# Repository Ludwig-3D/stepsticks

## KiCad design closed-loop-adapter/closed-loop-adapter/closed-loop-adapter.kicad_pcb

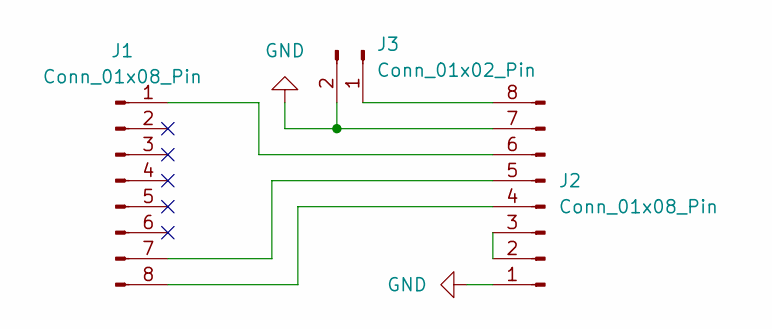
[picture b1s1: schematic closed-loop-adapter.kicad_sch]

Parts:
J1, J2: Conn_01x08_Pin; PinSocket_1x08_P2.54mm_Vertical
J3: Conn_01x02_Pin; JST_XH_S2B-XH-A-1_1x02_P2.50mm_Horizontal

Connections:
GND: J2.1, J2.7, J3.2
unnamed: J1.1, J2.6
unnamed: J1.7, J2.5
unnamed: J1.8, J2.4
unnamed: J2.2, J2.3
unnamed: J2.8, J3.1

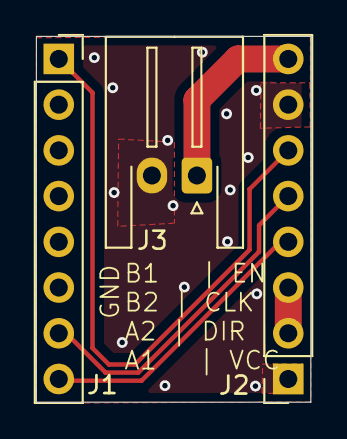
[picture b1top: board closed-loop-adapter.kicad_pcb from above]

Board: 2 copper layers, 15.2 x 20.3 mm, 3 parts (0 on the bottom side), 6 nets.

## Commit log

2024-05-30 feat: add initial upload for closed loop adapter
2024-05-30 feat: add initial schematic for closed loop bridge adapter
2024-08-06 feat: rework closed loop adapter
